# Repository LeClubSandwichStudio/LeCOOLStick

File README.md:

# GardenHack
Hack your garden with an open source monitoring device

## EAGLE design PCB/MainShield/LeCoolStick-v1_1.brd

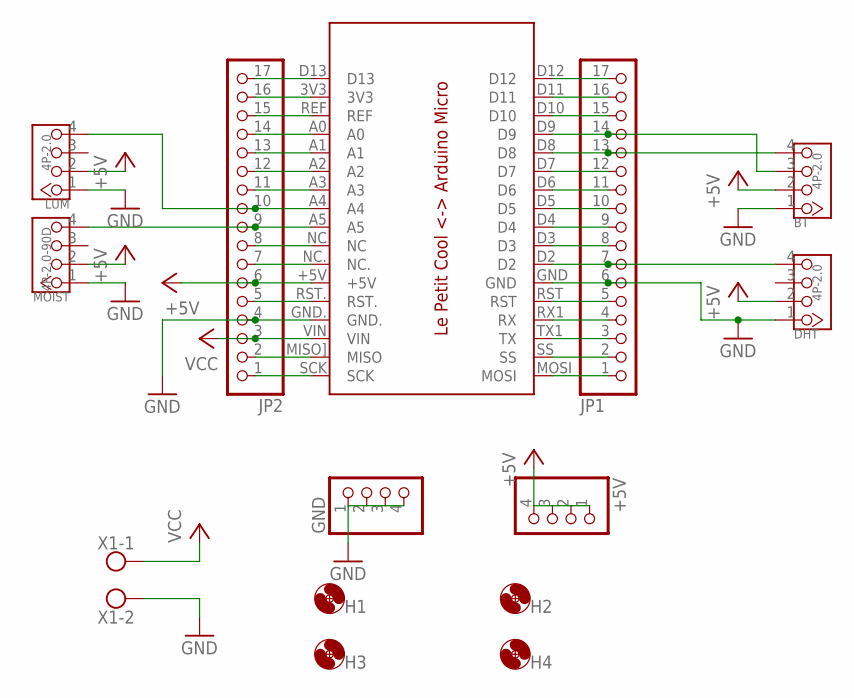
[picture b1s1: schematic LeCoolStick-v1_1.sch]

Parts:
+5V: PINHD-1X4; 1X04
BT: 4P-2.0
DHT: 4P-2.0
GND: PINHD-1X4; 1X04
H1, H2, H3, H4: MOUNT-HOLEHOLE-2.8; HOLE-2,8
JP1, JP2: PINHD-1X17; 1X17
LUM: 4P-2.0
MOIST: 4P-2.0-90D
PCB1: SHIELD_MICRO
X1: AK500/2

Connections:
3.3V: JP2.16, PCB1.3V3
+5V: +5V.1, +5V.2, +5V.3, +5V.4, BT.2, DHT.2, JP2.6, LUM.2, MOIST.2, PCB1.+5V
A0-FREE: JP2.14, PCB1.A0
A1-FREE: JP2.13, PCB1.A1
A2-FREE: JP2.12, PCB1.A2
A3-FREE: JP2.11, PCB1.A3
A4-LUM: JP2.10, LUM.4, PCB1.A4
A5-MOIST: JP2.9, MOIST.4, PCB1.A5
AREF: JP2.15, PCB1.REF
D0-RX1: JP1.4, PCB1.RX1 (RX)
D0-TX1: JP1.3, PCB1.TX1 (TX)
D2-DHT: DHT.4, JP1.7, PCB1.D2
D3-FREE: JP1.8, PCB1.D3
D4-FREE: JP1.9, PCB1.D4
D5-FREE: JP1.10, PCB1.D5
D6-FREE: JP1.11, PCB1.D6
D7-FREE: JP1.12, PCB1.D7
D8-BT(TX): BT.4, JP1.13, PCB1.D8
D9-BT(RX): BT.3, JP1.14, PCB1.D9
D10-FREE: JP1.15, PCB1.D10
D11-FREE: JP1.16, PCB1.D11
D12-FREE: JP1.17, PCB1.D12
D13-FREE: JP2.17, PCB1.D13
GND: BT.1, DHT.1, GND.1, GND.2, GND.3, GND.4, JP1.6, JP2.4, LUM.1, MOIST.1, PCB1.GND, PCB1.GND., X1.2
MISO-FREE: JP2.2, PCB1.MISO] (MISO)
MOSI-FREE: JP1.1, PCB1.MOSI
N/C: JP2.8, PCB1.NC
N/C.: JP2.7, PCB1.NC.
RST: JP1.5, PCB1.RST
RST.: JP2.5, PCB1.RST.
SCK-FREE: JP2.1, PCB1.SCK
SS-FREE: JP1.2, PCB1.SS
VCC: JP2.3, PCB1.VIN, X1.1

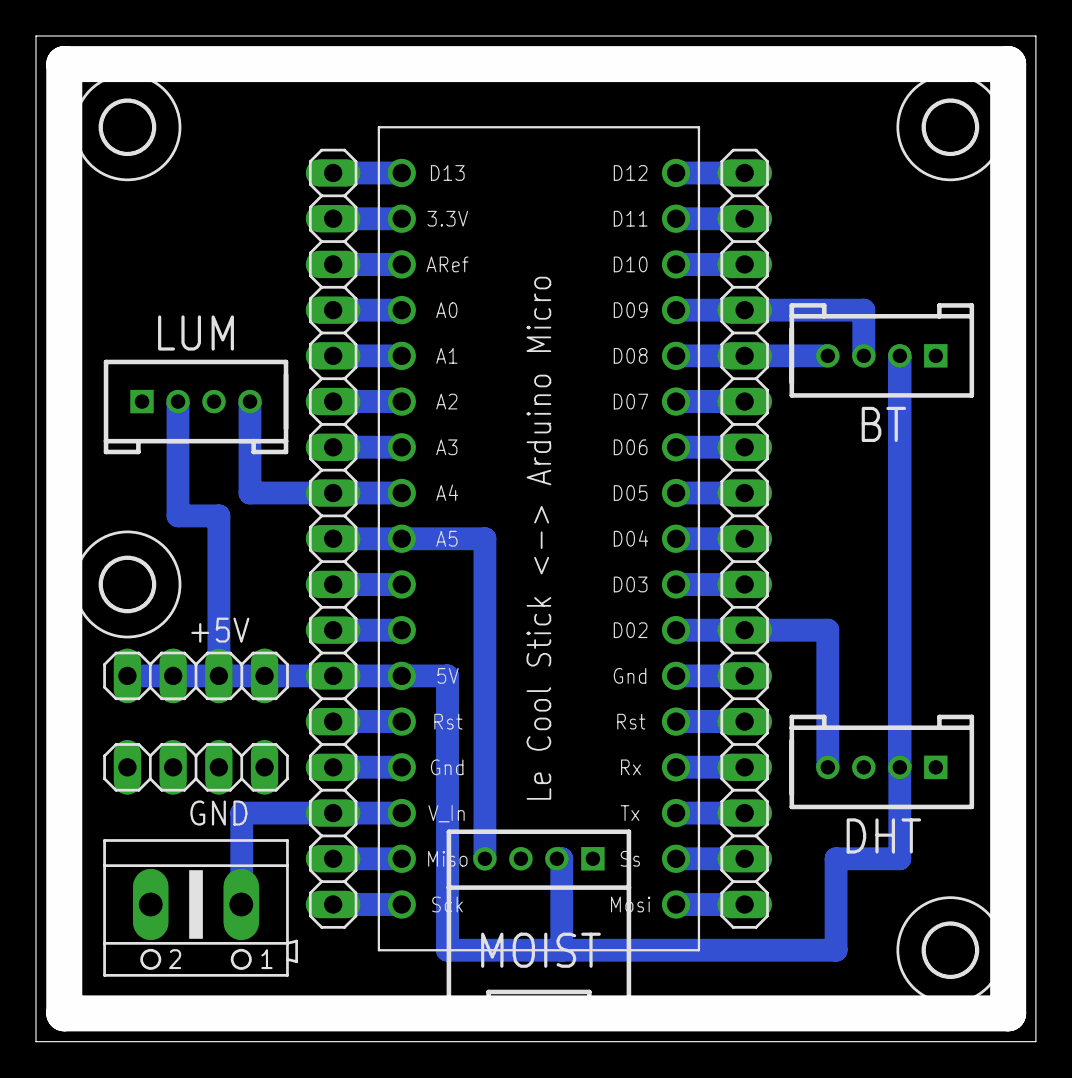
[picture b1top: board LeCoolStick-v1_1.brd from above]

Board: 2 copper layers, 53.5 x 53.9 mm, 14 parts (0 on the bottom side), 33 nets.

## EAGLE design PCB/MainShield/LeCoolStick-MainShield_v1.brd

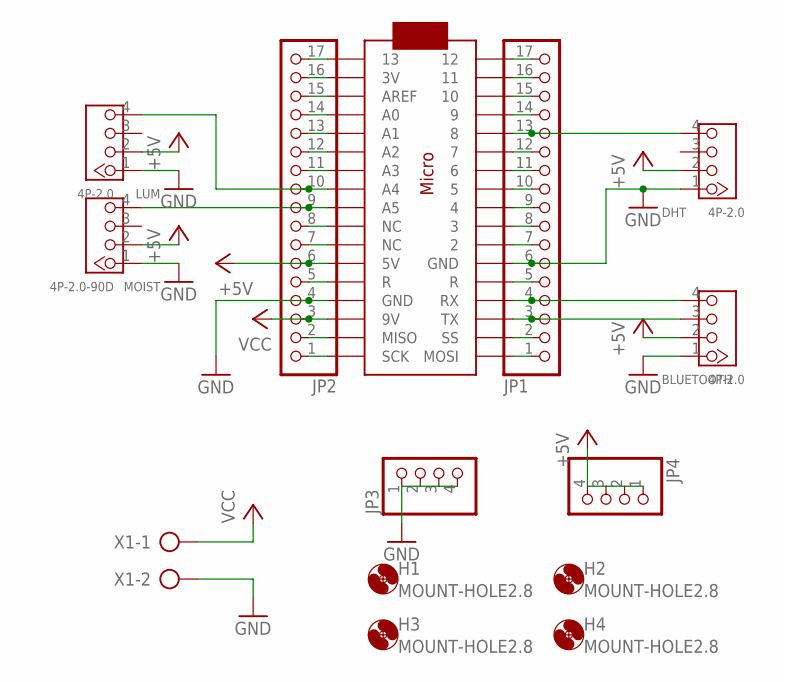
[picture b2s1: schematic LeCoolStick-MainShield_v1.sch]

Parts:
BLUETOOTH: 4P-2.0; HW4-2.0
DHT: 4P-2.0; HW4-2.0
H1, H2, H3, H4: MOUNT-HOLE2.8; 2,8
JP1, JP2: PINHD-1X17; 1X17
JP3, JP4: PINHD-1X4; 1X04
LUM: 4P-2.0; HW4-2.0
MOIST: 4P-2.0-90D; HW4-2.0-90D
U$1: ARDUINOMICRO
X1: AK500/2

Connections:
+5V: BLUETOOTH.2, DHT.2, JP2.6, JP4.1, JP4.2, JP4.3, JP4.4, LUM.2, MOIST.2, U$1.P$23 (5V)
GND: BLUETOOTH.1, DHT.1, JP1.6, JP2.4, JP3.1, JP3.2, JP3.3, JP3.4, LUM.1, MOIST.1, U$1.P$12 (GND), U$1.P$21 (GND), X1.2
unnamed: JP2.9, MOIST.4, U$1.P$26 (A5)
unnamed: JP2.10, LUM.4, U$1.P$27 (A4)
unnamed: DHT.4, JP1.13, U$1.P$5 (8)
unnamed: BLUETOOTH.4, JP1.4, U$1.P$14 (RX)
unnamed: BLUETOOTH.3, JP1.3, U$1.P$15 (TX)
unnamed: JP1.1, U$1.P$17 (MOSI)
unnamed: JP1.2, U$1.P$16 (SS)
unnamed: JP1.5, U$1.P$22 (R)
unnamed: JP1.7, U$1.P$11 (2)
unnamed: JP1.8, U$1.P$10 (3)
unnamed: JP1.9, U$1.P$9 (4)
unnamed: JP1.10, U$1.P$8 (5)
unnamed: JP1.11, U$1.P$7 (6)
unnamed: JP1.12, U$1.P$6 (7)
unnamed: JP1.14, U$1.P$4 (9)
unnamed: JP1.15, U$1.P$3 (10)
unnamed: JP1.16, U$1.P$2 (11)
unnamed: JP1.17, U$1.P$1 (12)
unnamed: JP2.1, U$1.P$18 (SCK)
unnamed: JP2.2, U$1.P$19 (MISO)
unnamed: JP2.5, U$1.P$13 (R)
unnamed: JP2.7, U$1.P$24 (NC)
unnamed: JP2.8, U$1.P$25 (NC)
unnamed: JP2.11, U$1.P$28 (A3)
unnamed: JP2.12, U$1.P$29 (A2)
unnamed: JP2.13, U$1.P$30 (A1)
unnamed: JP2.14, U$1.P$31 (A0)
unnamed: JP2.15, U$1.P$32 (AREF)
unnamed: JP2.16, U$1.P$33 (3V)
unnamed: JP2.17, U$1.P$34 (13)
VCC: JP2.3, U$1.P$20 (9V), X1.1

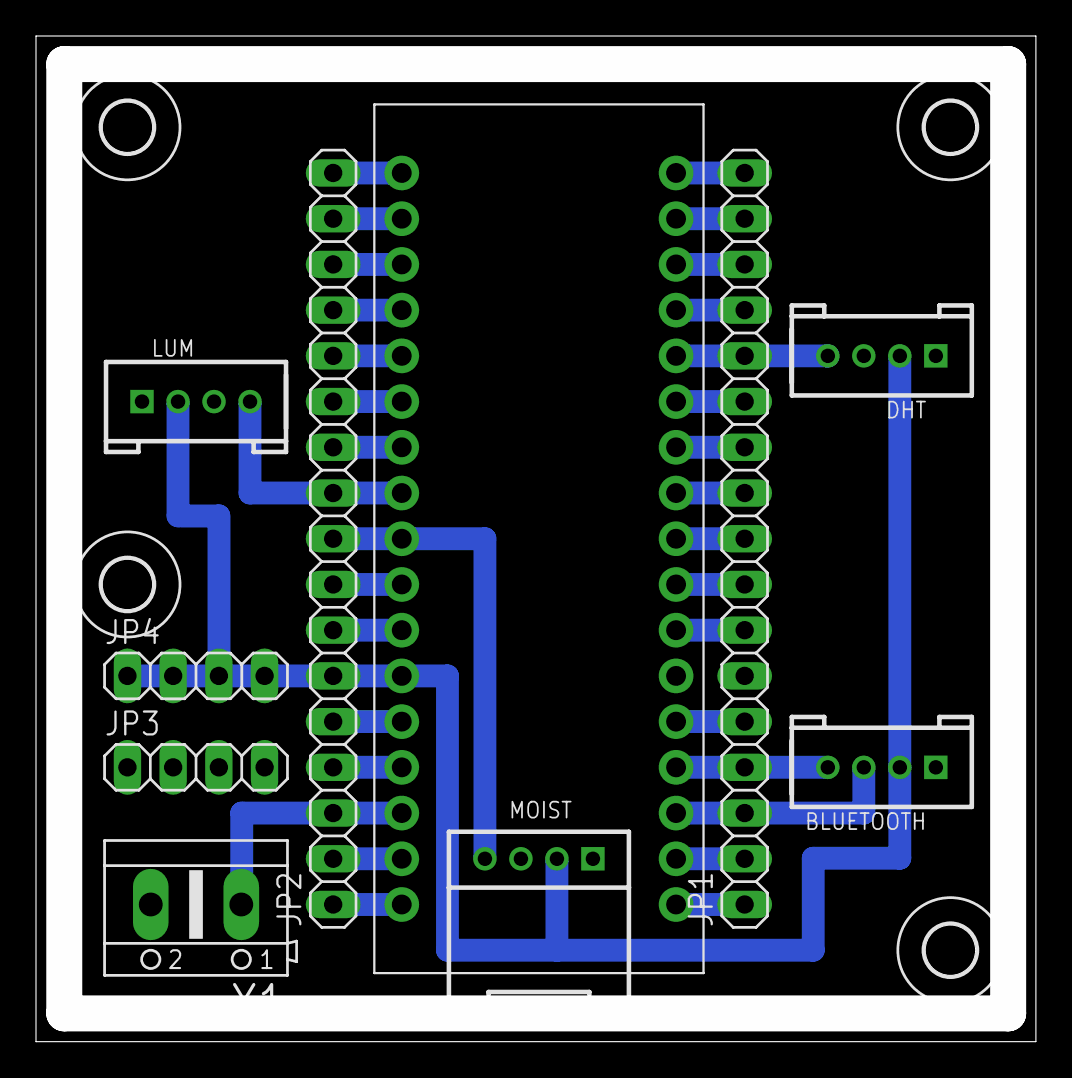
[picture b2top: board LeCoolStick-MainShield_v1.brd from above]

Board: 2 copper layers, 53.5 x 53.9 mm, 14 parts (0 on the bottom side), 33 nets.

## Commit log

2015-11-30 Le COOL Stick - PCB Main Shield V1.0
2015-11-30 Le COOL Stick V1.0
2015-11-30 Le COOL Stick PCB V1.0
2015-12-01 Le Cool Stick : Luminosity Sensing Library V1.0
2015-12-01 Le Cool Stick : Moisture Sensing Library V1.0
2015-12-01 Le Cool Stick : Temperature Sensing Library V1.0
2015-12-01 Le Cool Stick : Temperature & Humidity Sensing Library V1.0
2015-12-01 Le Cool Stick : Machine Intelligence V1.0
2015-12-01 Le Cool Stick : Arduino Sketch V1.0
2015-12-04 Le Cool Stick - PCB V1.1
2015-12-04 Le Cool Stick - Fichiers de prototypage PCB V1.1
2015-12-09 Le Cool Stick - Temperature & Humidity Sensing Library V1.0
2015-12-09 Le Cool Stick - Luminosity Sensing Library V1.0
2015-12-09 Le Cool Stick - Temperature Sensing Library V1.0
2015-12-09 Le Cool Stick - Moisture Sensing Library V1.0
2015-12-09 Le Cool Stick - Machine Intelligence Library V1.0
2015-12-09 La Cool Stick - Arduino Sketch V1.0
2015-12-09 Package LaCoolCo pour Eagle V1.0
2015-12-16 Le Cool Stick - Trace Foret 2 MM (Dessous) Release 1.1
2015-12-16 Le Cool Stick - Trace Foret 2 MM (Dessus) Release 1.1
2015-12-16 Le Cool Stick - Trace Pointe 60° Release 1.1
2015-12-16 Le Cool Stick - Fichier de percage Release 1.1
2015-12-16 Le Cool Stick - Fichier de Prototypage (GCode)
2015-12-22 Le Cool Stick - Dxf pour GCode V1.0
